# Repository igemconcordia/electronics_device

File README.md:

# electronics_device
This repository contains the electronic design files including schematics and PCB layout. The program used to read the files is KiCAD.

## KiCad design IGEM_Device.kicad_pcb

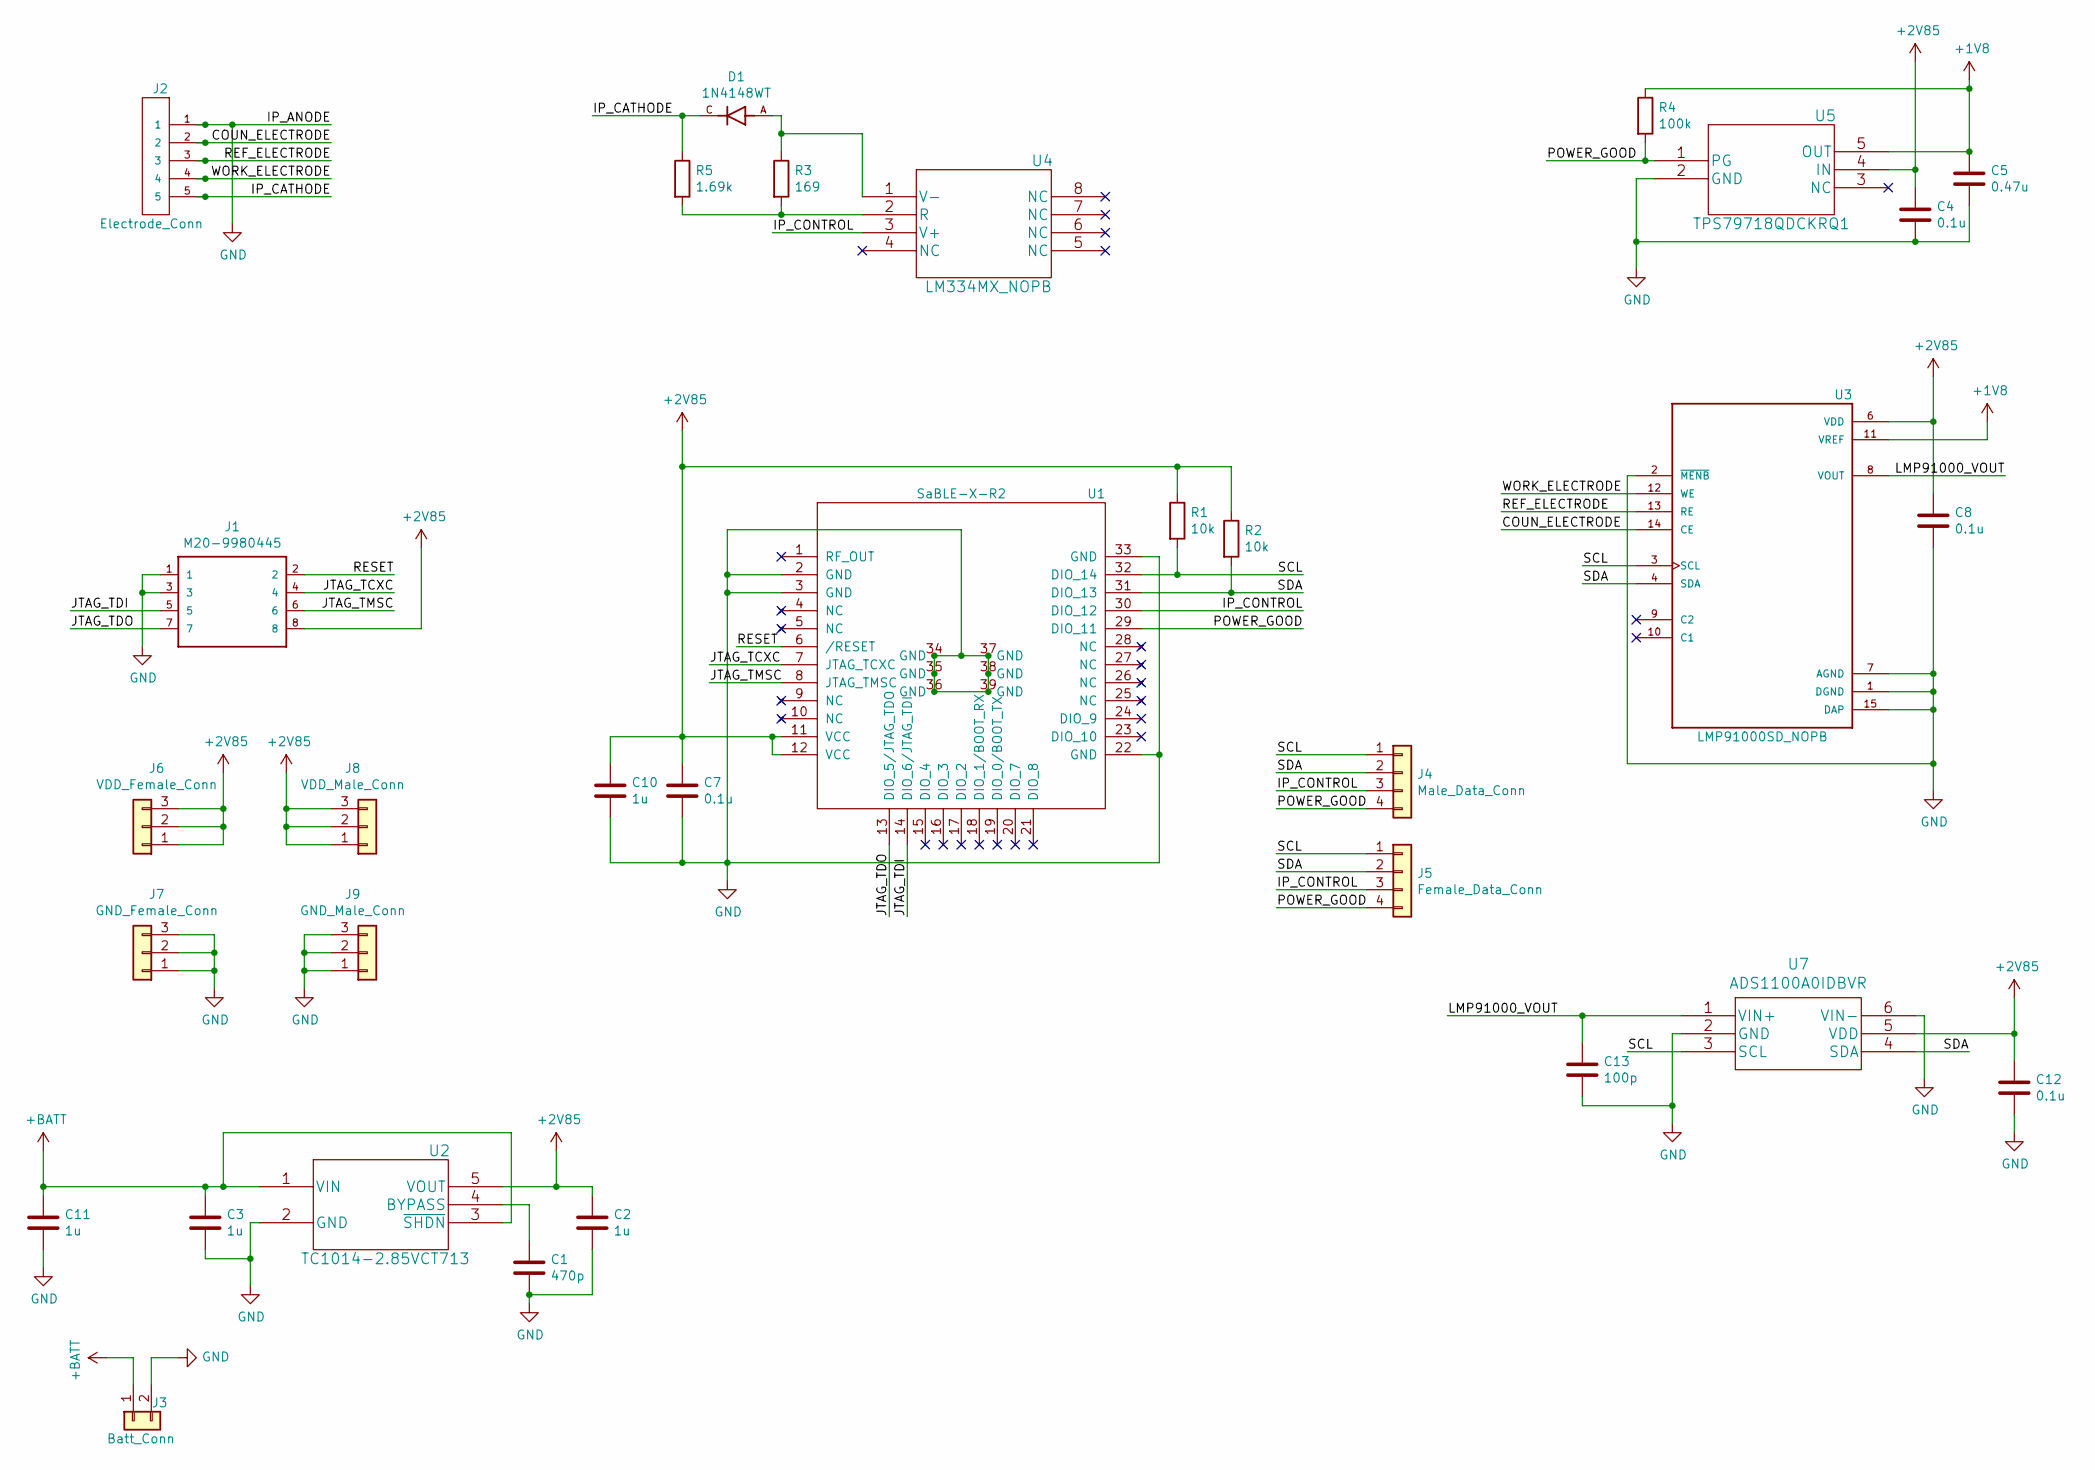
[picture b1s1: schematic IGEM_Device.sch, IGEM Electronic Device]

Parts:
C1: 470p; C_0805
C2, C3, C10, C11: 1u; C_0805
C4, C7, C8, C12: 0.1u; C_0805
C5: 0.47u; C_0805
C13: 100p; C_0805
D1: 1N4148WT; SODFL1608X70N
J1: M20-9980445; HDRV8W64P254_2X4_1016X508X910P
J2: Electrode_Conn; TSW-105-08-F-S-RA
J3: Batt_Conn; JST_S2B-PH-K-S(LF)(SN)
J4: Male_Data_Conn; HTSW-104-07-G-S
J5: Female_Data_Conn; 5-534237-2
J6: VDD_Female_Conn; 5-534237-1
J7: GND_Female_Conn; 5-534237-1
J8: VDD_Male_Conn; 5-146280-3
J9: GND_Male_Conn; 5-146280-3
R1, R2: 10k; R_0805
R3: 169; R_0805
R4: 100k; R_0805
R5: 1.69k; R_0805
U1: SaBLE-X-R2; 4500178C
U2: TC1014-2.85VCT713; TC1014-2.5VCT713
U3: LMP91000SD_NOPB; SON50P400X400X80-15N
U4: LM334MX_NOPB; LM334MX&slash_NOPB
U5: TPS79718QDCKRQ1
U7: ADS1100A0IDBVR

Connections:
+1V8: C5.1, R4.1, U3.11 (VREF), U5.5 (OUT)
+2V85: C2.1, C4.1, C7.1, C8.1, C10.1, C12.1, J1.8, J6.1, J6.2, J6.3, J8.1, J8.2, J8.3, R1.1, R2.1, U1.11 (VCC), U1.12 (VCC), U2.5 (VOUT), U3.6 (VDD), U5.4 (IN), U7.5 (VDD)
+BATT: C3.1, C11.1, J3.1, U2.1 (VIN), U2.3 (~SHDN)
/COUN_ELECTRODE: J2.2, U3.14 (CE)
/IP_CATHODE: D1.C, J2.5, R5.1
/IP_CONTROL: J4.3, J5.3, U1.30 (DIO_12), U4.3 (V+)
/JTAG_TCXC: J1.4, U1.7 (JTAG_TCXC)
/JTAG_TDI: J1.5, U1.14 (DIO_6/JTAG_TDI)
/JTAG_TDO: J1.7, U1.13 (DIO_5/JTAG_TDO)
/JTAG_TMSC: J1.6, U1.8 (JTAG_TMSC)
/LMP91000_VOUT: C13.1, U3.8 (VOUT), U7.1 (VIN+)
/POWER_GOOD: J4.4, J5.4, R4.2, U1.29 (DIO_11), U5.1 (PG)
/REF_ELECTRODE: J2.3, U3.13 (RE)
/RESET: J1.2, U1.6 (/RESET)
/SCL: J4.1, J5.1, R1.2, U1.32 (DIO_14), U3.3 (SCL), U7.3 (SCL)
/SDA: J4.2, J5.2, R2.2, U1.31 (DIO_13), U3.4 (SDA), U7.4 (SDA)
/WORK_ELECTRODE: J2.4, U3.12 (WE)
GND: C1.2, C2.2, C3.2, C4.2, C5.2, C7.2, C8.2, C10.2, C11.2, C12.2, C13.2, J1.1, J1.3, J2.1, J3.2, J7.1, J7.2, J7.3, J9.1, J9.2, J9.3, U1.2 (GND), U1.3 (GND), U1.22 (GND), U1.33 (GND), U1.34 (GND), U1.35 (GND), U1.36 (GND), U1.37 (GND), U1.38 (GND), U1.39 (GND), U2.2 (GND), U3.1 (DGND), U3.2 (~MENB~), U3.7 (AGND), U3.15 (DAP), U5.2 (GND), U7.2 (GND), U7.6 (VIN-)
unnamed: C1.1, U2.4 (BYPASS)
unnamed: D1.A, R3.1, U4.1 (V-)
unnamed: R3.2, R5.2, U4.2 (R)

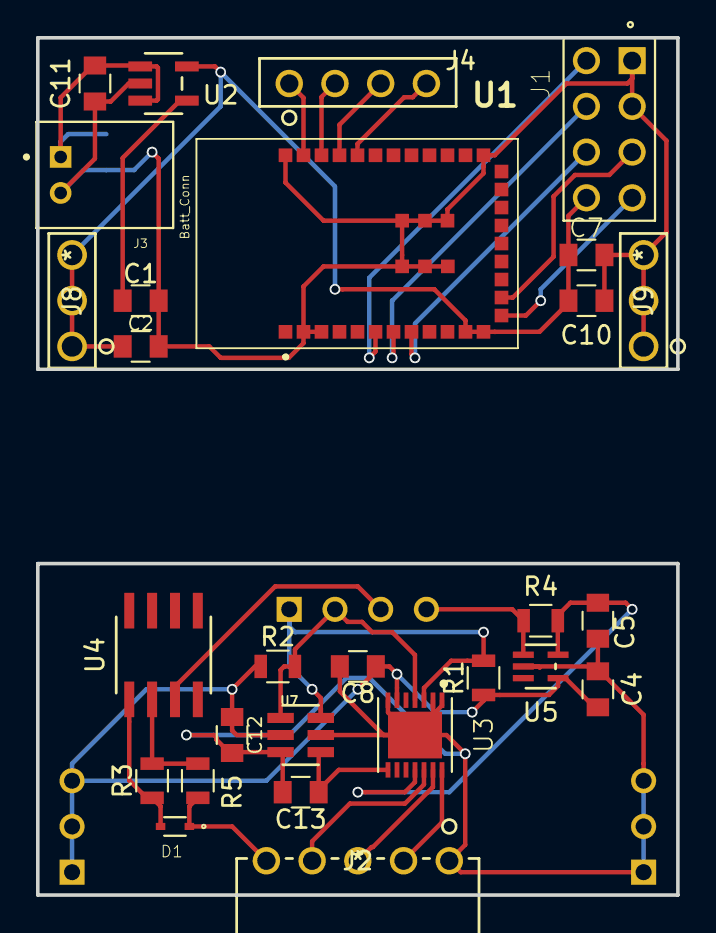
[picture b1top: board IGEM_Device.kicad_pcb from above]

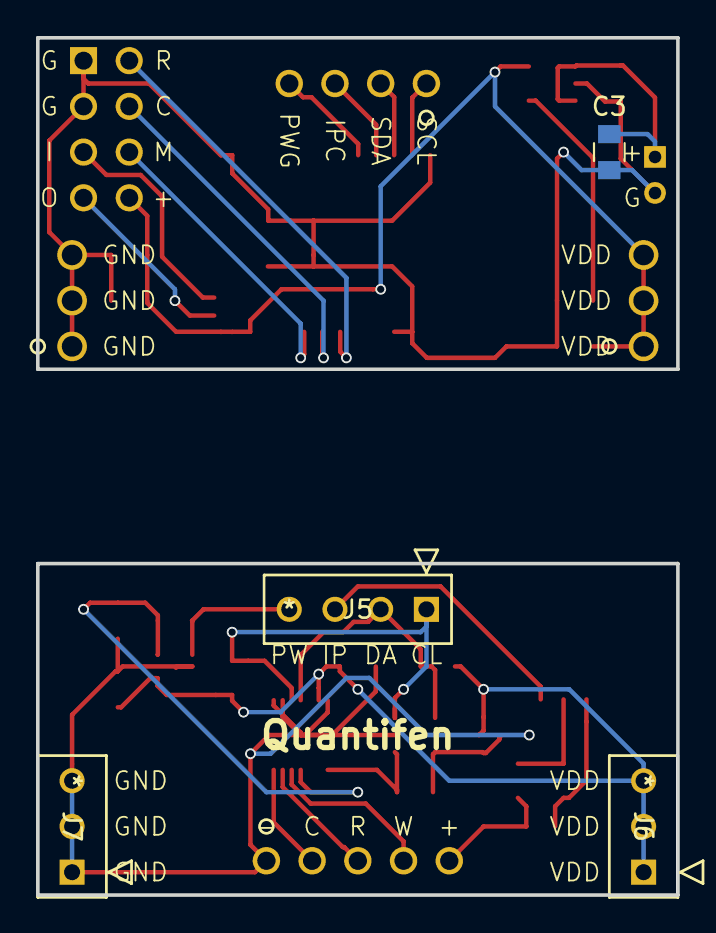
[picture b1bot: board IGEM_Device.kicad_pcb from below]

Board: 2 copper layers, 35.6 x 47.6 mm, 32 parts (4 on the bottom side), 21 nets.

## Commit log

2019-06-08 s Please enter the commit message for your changes. Lines starting
2019-06-08 Kicad v2.1
2019-06-09 schem v2.2
2019-06-09 Added C12
2019-06-09 Associated most footprints to their symbols
2019-06-21 PCB v1
2019-06-27 Update to PCB and Gerber files
2019-07-08 Minor changes
2019-07-22 Added ADC
2019-08-11 Minor fixes
2019-08-29 Updated layout, added 3D shapes and Gerber files

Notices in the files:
parts and their libraries:
Copyright 2016 Accelerated Designs. All rights reserved.
